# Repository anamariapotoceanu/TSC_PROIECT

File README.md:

# OpenBook E-Reader

OpenBook este un e-reader open-source construit in jurul microcontrollerului ESP32-C6-WROOM-1. Dispozitivul ofera o experienta de lectura cu afisaj e-paper, butoane fizice, conectivitate wireless si senzori de mediu integrati.

## DIAGRAMA BLOC

## BOM

| DENUMIRE | SITE ACHIZITIONARE | DATASHEET |
|----------|---------------------|-----------|
| BOOT_BUTON | [LINK](https://www.snapeda.com/parts/EVQP7L01P/Panasonic%20Electronic%20Components/view-part/?welcome=home) | [LINK](https://www.snapeda.com/parts/EVQP7L01P/Panasonic/datasheet/) |
| C1 - C10 | [LINK](https://componentsearchengine.com/part-view/CC0402MRX5R5BB106/YAGEO) | [LINK](https://componentsearchengine.com/Datasheets/2/CC0402MRX5R5BB106.pdf) |
| C1_BAT | [LINK](https://componentsearchengine.com/part-view/CC0402MRX5R5BB106/YAGEO) | [LINK](https://componentsearchengine.com/Datasheets/2/CC0402MRX5R5BB106.pdf) |
| C1_BAT2 | [LINK](https://componentsearchengine.com/part-view/CC0402MRX5R5BB106/YAGEO) | [LINK](https://componentsearchengine.com/Datasheets/2/CC0402MRX5R5BB106.pdf) |
| C2_BAT | [LINK](https://componentsearchengine.com/part-view/CC0402MRX5R5BB106/YAGEO) | [LINK](https://componentsearchengine.com/Datasheets/2/CC0402MRX5R5BB106.pdf) |
| C4_USB | [LINK](https://componentsearchengine.com/part-view/CC0402MRX5R5BB106/YAGEO) | [LINK](https://componentsearchengine.com/Datasheets/2/CC0402MRX5R5BB106.pdf) |
| C5_USB | [LINK](https://componentsearchengine.com/part-view/CC0402MRX5R5BB106/YAGEO) | [LINK](https://componentsearchengine.com/Datasheets/2/CC0402MRX5R5BB106.pdf) |
| C10_SUPERCAR | [LINK](https://industry.panasonic.com/global/en/products/control/switch/light-touch/number/evqpuj02k) | [LINK](https://industry.panasonic.com/global/en/downloads?tab=catalog&small_g_cd=203&part_no=EVQPUJ02K) |
| CHANGE_BUTTON | [LINK](https://www.snapeda.com/parts/EVQP7L01P/Panasonic%20Electronic%20Components/view-part/?welcome=home) | [LINK](https://www.snapeda.com/parts/EVQP7L01P/Panasonic/datasheet/) |
| CHG_LED | [LINK](https://www.snapeda.com/parts/KP-1608SURCK/Kingbright/view-part/?ref=search&t=LED%200603) | [LINK](https://www.snapeda.com/parts/KP-1608SURCK/Kingbright/datasheet/) |
| C_DELAY | [LINK](https://componentsearchengine.com/part-view/CC0402MRX5R5BB106/YAGEO) | [LINK](https://componentsearchengine.com/Datasheets/2/CC0402MRX5R5BB106.pdf) |
| D1 | [LINK](https://www.snapeda.com/parts/USBLC6-2SC6Y/STMicroelectronics/view-part/?ref=eda) | [LINK](https://www.snapeda.com/parts/USBLC6-2SC6Y/STMicroelectronics/view-part/?ref=eda) |
| D2 | [LINK](https://ro.mouser.com/ProductDetail/KYOCERA-AVX/SD0805S020S1R0?qs=jCA%252BPfw4LHbpkAoSnwrdjw%3D%3D) | [LINK](https://ro.mouser.com/datasheet/2/40/schottky-3165252.pdf) |
| D3 | [LINK](https://ro.mouser.com/ProductDetail/KYOCERA-AVX/SD0805S020S1R0?qs=jCA%252BPfw4LHbpkAoSnwrdjw%3D%3D) | [LINK](https://ro.mouser.com/datasheet/2/40/schottky-3165252.pdf) |
| D4 | [LINK](https://ro.mouser.com/ProductDetail/KYOCERA-AVX/SD0805S020S1R0?qs=jCA%252BPfw4LHbpkAoSnwrdjw%3D%3D) | [LINK](https://ro.mouser.com/datasheet/2/40/schottky-3165252.pdf) |
| D5 | [LINK](https://ro.mouser.com/ProductDetail/KYOCERA-AVX/SD0805S020S1R0?qs=jCA%252BPfw4LHbpkAoSnwrdjw%3D%3D) | [LINK](https://ro.mouser.com/datasheet/2/40/schottky-3165252.pdf) |
| D6 | [LINK](https://www.snapeda.com/parts/PGB1010603MR/Littelfuse/view-part/?ref=eda) | [LINK](https://www.snapeda.com/parts/PGB1010603MR/Littelfuse%20Inc./datasheet/) |
| D7 | [LINK](https://ro.mouser.com/ProductDetail/KYOCERA-AVX/SD0805S020S1R0?qs=jCA%252BPfw4LHbpkAoSnwrdjw%3D%3D) | [LINK](https://ro.mouser.com/datasheet/2/40/schottky-3165252.pdf) |
| D8 | [LINK](https://www.snapeda.com/parts/PGB1010603MR/Littelfuse/view-part/?ref=eda) | [LINK](https://www.snapeda.com/parts/PGB1010603MR/Littelfuse%20Inc./datasheet/) |
| D9 | [LINK](https://www.snapeda.com/parts/PGB1010603MR/Littelfuse/view-part/?ref=eda) | [LINK](https://www.snapeda.com/parts/PGB1010603MR/Littelfuse%20Inc./datasheet/) |
| D10 | [LINK](https://www.snapeda.com/parts/PGB1010603MR/Littelfuse/view-part/?ref=eda) | [LINK](https://www.snapeda.com/parts/PGB1010603MR/Littelfuse%20Inc./datasheet/) |
| D11 | [LINK](https://www.snapeda.com/parts/PGB1010603MR/Littelfuse/view-part/?ref=eda) | [LINK](https://www.snapeda.com/parts/PGB1010603MR/Littelfuse%20Inc./datasheet/) |
| D12 | [LINK](https://www.snapeda.com/parts/PGB1010603MR/Littelfuse/view-part/?ref=eda) | [LINK](https://www.snapeda.com/parts/PGB1010603MR/Littelfuse%20Inc./datasheet/) |
| EPD_C1 - EPD_C12 | [LINK](https://componentsearchengine.com/part-view/CC0402MRX5R5BB106/YAGEO) | [LINK](https://componentsearchengine.com/Datasheets/2/CC0402MRX5R5BB106.pdf) |
| IC1 | [LINK](https://componentsearchengine.com/part-view/BD5229G-TR/ROHM%20Semiconductor) | [LINK](https://datasheet.datasheetarchive.com/originals/distributors/Datasheets_SAMA/f2b9741ef86007909f138d561a359946.pdf) |
| IC4 | [LINK](https://componentsearchengine.com/part-view/XC6220A331MR-G/Torex) | [LINK](https://product.torexsemi.com/system/files/series/xc6220.pdf) |
| J1 | [LINK](https://componentsearchengine.com/part-view/FH34SRJ-24S-0.5SH(99)/Hirose) | [LINK](https://www.hirose.com/en/product/document?clcode=CL0580-1255-6-99&productname=FH34SRJ-24S-0.5SH(99)&series=FH34SRJ&documenttype=2DDrawing&lang=en&documentid=0000990903) |
| J2 | [LINK](https://componentsearchengine.com/part-view/USB4110-GF-A/GCT%20(GLOBAL%20CONNECTOR%20TECHNOLOGY)) | [LINK](https://gct.co/files/drawings/usb4110.pdf) |
| J3 | [LINK](https://www.snapeda.com/parts/PRT-14417/SparkFun/view-part/) | [LINK](https://www.snapeda.com/parts/PRT-14417/SparkFun%20Electronics/datasheet/) |
| J4 | [LINK](https://www.snapeda.com/parts/112A-TAAR-R03/Attend/view-part/) | [LINK](https://www.snapeda.com/parts/112A-TAAR-R03/Attend/datasheet/) |
| MCP73831 | [LINK](https://ro.mouser.com/ProductDetail/Microchip-Technology/MCP73831T-2ACI-OT?qs=yUQqVecv4qvbBQBGbHx0Mw%3D%3D&utm_id=20109199409&utm_source=google&utm_medium=cpc&utm_marketing_tactic=emeacorp&gad_source=1&gbraid=0AAAAADn_wf0-USzm1eg1ywGvQg_qMgG3H) | [LINK](https://ro.mouser.com/datasheet/2/268/MCP73831_Family_Data_Sheet_DS20001984H-3441711.pdf) |
| L1 | [LINK](https://ro.mouser.com/ProductDetail/Wurth-Elektronik/744043680?qs=PGXP4M47uW6VkZq%252BkzjrHA%3D%3D) | [LINK](https://www.we-online.com/components/products/datasheet/744043680.pdf) |
| PFMF.050.1 | [LINK](https://ro.mouser.com/ProductDetail/EPCOS-TDK/B72520T0350K062?qs=dEfas%2FXlABIszF52uu7vrg%3D%3D) | [LINK](https://www.tdk-electronics.tdk.com/inf/75/db/CTVS_14/Surge_protection_series.pdf) |
| Q1 | [LINK](https://componentsearchengine.com/part-view/DMG2305UX-7/Diodes%20Incorporated) | [LINK](https://www.diodes.com//assets/Datasheets/DMG2305UX.pdf) |
| Q2 | [LINK](https://componentsearchengine.com/part-view/DMG2305UX-7/Diodes%20Incorporated) | [LINK](https://www.diodes.com//assets/Datasheets/DMG2305UX.pdf) |
| Q3 | [LINK](https://componentsearchengine.com/part-view/SI1308EDL-T1-GE3/Vishay) | [LINK](https://componentsearchengine.com/part-view/SI1308EDL-T1-GE3/Vishay) |
| R1 - R10 | [LINK](https://componentsearchengine.com/part-view/R0402%201%25%20100%20K%20(RC0402FR-07100KL)/YAGEO) | [LINK](https://www.yageo.com/upload/media/product/products/datasheet/rchip/PYu-RC_Group_51_RoHS_L_12.pdf) |
| R1_PINH | [LINK](https://componentsearchengine.com/part-view/R0402%201%25%20100%20K%20(RC0402FR-07100KL)/YAGEO) | [LINK](https://www.yageo.com/upload/media/product/products/datasheet/rchip/PYu-RC_Group_51_RoHS_L_12.pdf) |
| R1_PINH1 | [LINK](https://componentsearchengine.com/part-view/R0402%201%25%20100%20K%20(RC0402FR-07100KL)/YAGEO) | [LINK](https://www.yageo.com/upload/media/product/products/datasheet/rchip/PYu-RC_Group_51_RoHS_L_12.pdf) |
| R1_BAT | [LINK](https://componentsearchengine.com/part-view/R0402%201%25%20100%20K%20(RC0402FR-07100KL)/YAGEO) | [LINK](https://www.yageo.com/upload/media/product/products/datasheet/rchip/PYu-RC_Group_51_RoHS_L_12.pdf) |
| R1_PWRUSB | [LINK](https://componentsearchengine.com/part-view/R0402%201%25%20100%20K%20(RC0402FR-07100KL)/YAGEO) | [LINK](https://www.yageo.com/upload/media/product/products/datasheet/rchip/PYu-RC_Group_51_RoHS_L_12.pdf) |
| R2_PINH | [LINK](https://componentsearchengine.com/part-view/R0402%201%25%20100%20K%20(RC0402FR-07100KL)/YAGEO) | [LINK](https://www.yageo.com/upload/media/product/products/datasheet/rchip/PYu-RC_Group_51_RoHS_L_12.pdf) |
| R2-PINH1 | [LINK](https://componentsearchengine.com/part-view/R0402%201%25%20100%20K%20(RC0402FR-07100KL)/YAGEO) | [LINK](https://www.yageo.com/upload/media/product/products/datasheet/rchip/PYu-RC_Group_51_RoHS_L_12.pdf) |
| R2_USB | [LINK](https://componentsearchengine.com/part-view/R0402%201%25%20100%20K%20(RC0402FR-07100KL)/YAGEO) | [LINK](https://www.yageo.com/upload/media/product/products/datasheet/rchip/PYu-RC_Group_51_RoHS_L_12.pdf) |
| R2_USB1 | [LINK](https://componentsearchengine.com/part-view/R0402%201%25%20100%20K%20(RC0402FR-07100KL)/YAGEO) | [LINK](https://www.yageo.com/upload/media/product/products/datasheet/rchip/PYu-RC_Group_51_RoHS_L_12.pdf) |
| RESET_BUTTON | [LINK](https://www.snapeda.com/parts/EVQP7L01P/Panasonic%20Electronic%20Components/view-part/?welcome=home) | [LINK](https://www.snapeda.com/parts/EVQP7L01P/Panasonic/datasheet/) |
| R_BOOT | [LINK](https://componentsearchengine.com/part-view/R0402%201%25%20100%20K%20(RC0402FR-07100KL)/YAGEO) | [LINK](https://www.yageo.com/upload/media/product/products/datasheet/rchip/PYu-RC_Group_51_RoHS_L_12.pdf) |
| R_CAPACITOR | [LINK](https://componentsearchengine.com/part-view/R0402%201%25%20100%20K%20(RC0402FR-07100KL)/YAGEO) | [LINK](https://www.yageo.com/upload/media/product/products/datasheet/rchip/PYu-RC_Group_51_RoHS_L_12.pdf) |
| R_CHANGE | [LINK](https://componentsearchengine.com/part-view/R0402%201%25%20100%20K%20(RC0402FR-07100KL)/YAGEO) | [LINK](https://www.yageo.com/upload/media/product/products/datasheet/rchip/PYu-RC_Group_51_RoHS_L_12.pdf) |
| R_CL1 | [LINK](https://componentsearchengine.com/part-view/R0402%201%25%20100%20K%20(RC0402FR-07100KL)/YAGEO) | [LINK](https://www.yageo.com/upload/media/product/products/datasheet/rchip/PYu-RC_Group_51_RoHS_L_12.pdf) |
| R_RESET | [LINK](https://componentsearchengine.com/part-view/R0402%201%25%20100%20K%20(RC0402FR-07100KL)/YAGEO) | [LINK](https://www.yageo.com/upload/media/product/products/datasheet/rchip/PYu-RC_Group_51_RoHS_L_12.pdf) |
| SENSOR2 | [LINK](https://www.snapeda.com/parts/BME680/Bosch/view-part/?welcome=home) | [LINK](https://www.snapeda.com/parts/BME680/Bosch%20Sensortec/datasheet/) |
| TP | [nan](nan) | [nan](nan) |
| U1 | [LINK](https://www.snapeda.com/parts/W25Q512JVEIQ/Winbond+Electronics/view-part/?ref=eda) | [LINK](https://www.snapeda.com/parts/W25Q512JVEIQ/Winbond+Electronics/view-part/?ref=eda) |
| U2 | [LINK](https://www.snapeda.com/parts/ESP32-C6-WROOM-1-N8/Espressif+Systems/view-part/?ref=eda) | [LINK](https://www.snapeda.com/parts/ESP32-C6-WROOM-1-N8/Espressif%20Systems/datasheet/) |
| U3 | [LINK](https://www.snapeda.com/parts/DS3231SN%23/Analog+Devices/view-part/?ref=eda) | [LINK](https://www.snapeda.com/parts/DS3231SN%23/Analog%20Devices/datasheet/) |
| U4 | [LINK](https://www.snapeda.com/parts/MAX17048G+T10/Analog+Devices/view-part/?ref=eda) | [LINK ](https://www.snapeda.com/parts/MAX17048G+T10/Analog%20Devices/datasheet/) |

## Functionalitate hardware detaliata

OpenBook este un e-reader open-source construit in jurul microcontrollerului ESP32-C6-WROOM-1-N8. Sistemul este modular si a fost gandit pentru consum redus de energie, simplitate si extensibilitate.

### Microcontroller - ESP32-C6-WROOM-1-N8
- Procesor RISC-V 32-bit, frecventa 160 MHz+
- Suport pentru Wi-Fi 6, BLE 5 si USB 2.0 FS
- Interfete disponibile: SPI, I2C, UART, GPIO
- Consum redus: aproximativ 60 mA in activ, sub 100 uA in deep sleep

### Display - E-Paper 7.5 inch (Waveshare)
- Rezolutie 800x480 alb-negru
- Interfata SPI, partajata cu alte periferice
- Foloseste linii dedicate pentru ceas, date, comenzi, reset si status
- Consum doar in timpul refreshului (~30 - 50 mA)

### Senzori de mediu
- **BME688** masoara temperatura, umiditatea, presiunea si calitatea aerului
- Conectat pe magistrala I2C, alaturi de RTC si fuel gauge
- **DS3231**  este un RTC cu backup pe supercapacitor si semnal de intrerupere catre microcontroller
- **MAX17048** (fuel gauge): I2C + ALERT pe IO16
- Un fuel gauge care poate trimite alerta in caz de nivel scazut

### Memorie externa
- W25Q512J, o memorie NOR Flash de 64MB, conectata prin SPI
- Are chip select dedicat pentru acces independent de afisaj

### SD Card (optional)
- Suportat pe aceeasi magistrala SPI cu chip select separat
- Permite extinderea capacitatii de stocare

### Butoane
- Trei butoane tactile conectate direct la pinii microcontrollerului
- Sunt folosite pentru navigare si selectie in interfata
- Gestionate prin intreruperi, cu debounce hardware si software

### Alimentare
- Sistemul este alimentat de o baterie Li-Po de 2500 mAh
- Incarcarea se face prin USB-C cu ajutorul unui MCP73831
- Un semnal digital permite monitorizarea starii de incarcare
- Tensiunea este stabilizata la 3.3V printr-un LDO

### USB-C
- Asigura incarcare si transfer de fisiere in mod MSC (Mass Storage)
- Liniile USB sunt protejate cu diode ESD

### Consum estimativ
- In activ cu Wi-Fi: intre 60 si 100 mA
- In activ fara Wi-Fi: intre 40 si 60 mA
- In standby: aproximativ 10 mA
- In deep sleep: sub 100 uA

### PCB si carcasa
- Placa in 2 straturi, rutare clara pentru alimentare si SPI
- Separare intre zonele digitale si analogice
- Carcasa ABS/PC, usoara si ergonomica

| IO Pin | Semnal     | Rol                                               |
|--------|------------|----------------------------------------------------|
| EN | RESET  | Semnal de intrare pentru resetare |
| 0| INT_RTC | Semnal de intrerupere generat de modulul RTC |
| 1 | 32KHZ | Oscilator 32kHz pentru RTC |
| 2 | MISO | SPI MISO date de la periferice |
| 3 | EPD_BUSY | Semnal ocupat de la afisaj e-paper |
| 4 | SS_SD | Chip Select pentru SD Card |
| 5 | EPD_DC | Comanda date/controle pentru e-paper |
| 6 | SCK | SPI Clock comun pentru SD, flash si e-paper |
| 7 | MOSI | SPI MOSI date catre SD, flash, e-paper |
| 8 | GPIO8 | Selectarea cardului SD |
| 9 | IO/BOOT | Mod de boot selectabil |
| 10 | EPD_CS | Chip Select pentru afisaj e-paper |
| 11 | FLASH_CS | Chip Select pentru flash NOR |
| 12 | USB_D- | Linie pozitiva pentru USB Full-Speed |
| 13 | USB_D+ | Linie pozitiva pentru USB Full-Speed |
| 14 | NEUTILIZAT | NEUTILIZAT |
| 15 | IO/CHANGE | Detectarea modificarii starii |
| 16 | TX | Debug |
| 17 | RX | Debug |
| 18 | RTC_RST | Reset pentru modulul RTC|
| 19 | I2C_PW | Gestionarea alimentarii pentru dispozitivele I2C |
| 20 | EPD_3V3_C | Gestionarea alimentarii display-ului |
| 21 | SDA | I2C SDA conexiune alternativa RTC |
| 22 | SCL | I2C SCL conexiune alternativa RTC |
| 23 | EPD_RST | Reset alternativ e-paper display |

## Erori

Am aprobat erorile din schematic deoarece alimentarile sunt corecte din punct de vedere hardware.

Am aprobat erorile de DRC aparute la mufa USB din cauza celor doua gauri, deoarece acestea sunt conforme cu specificatiile
mecanice ale mufei si nu afecteaza functionalitatea.

## Imagini

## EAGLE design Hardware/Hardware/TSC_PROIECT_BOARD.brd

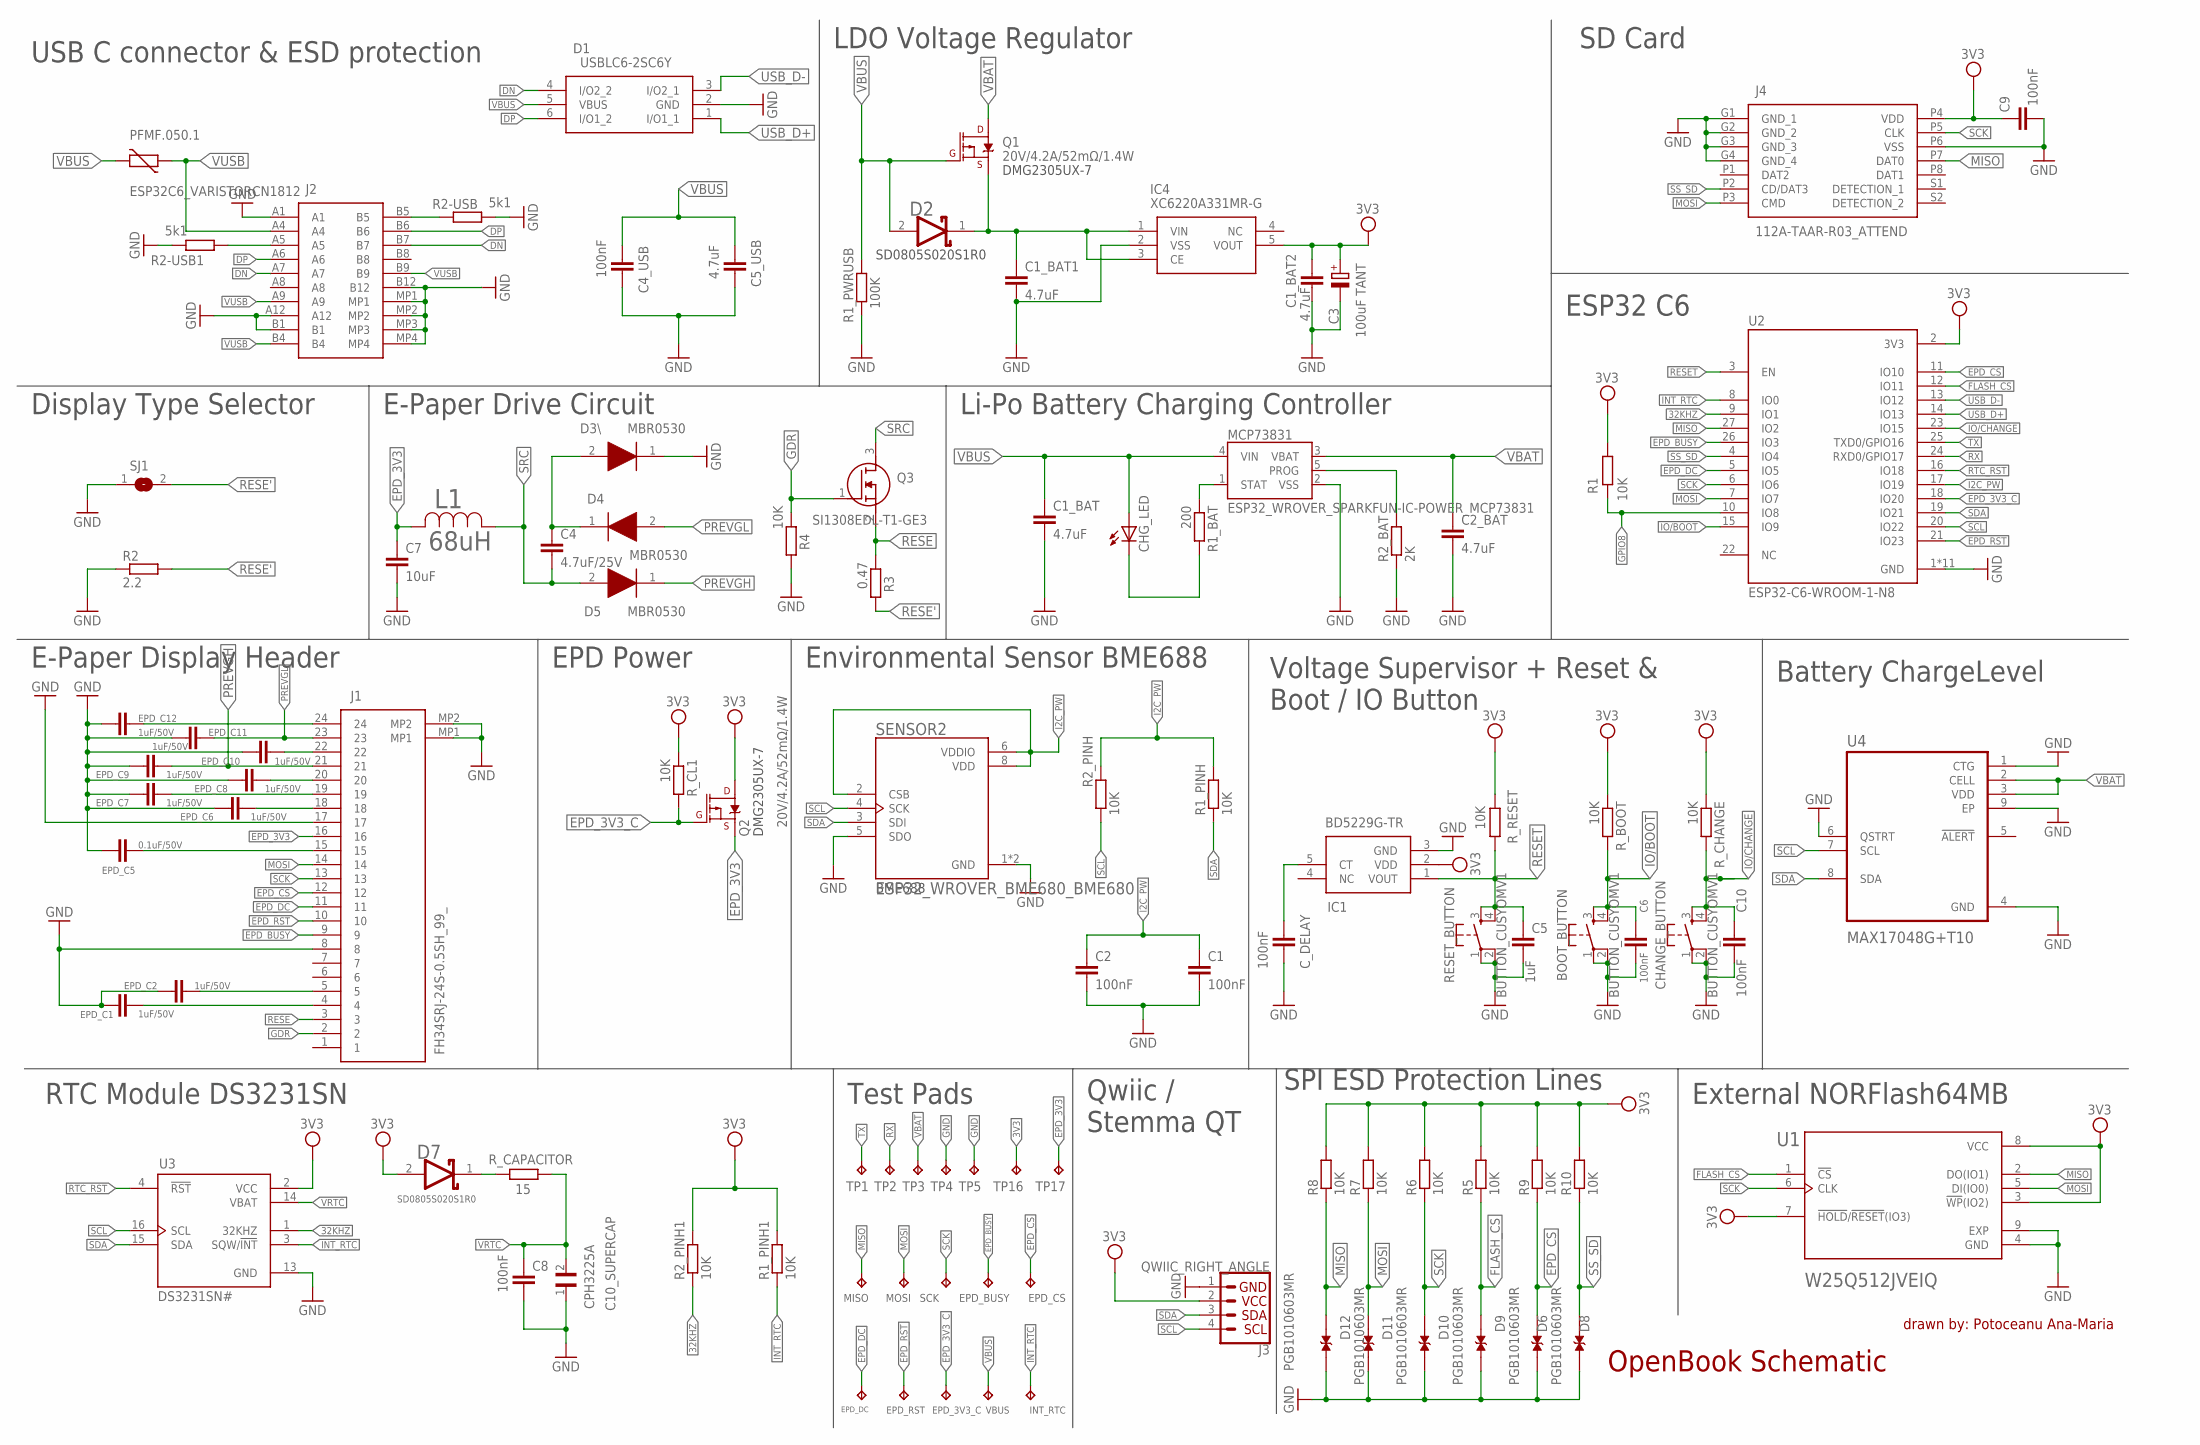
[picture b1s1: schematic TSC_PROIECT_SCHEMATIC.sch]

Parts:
BOOT_BUTTON: BUTTON_CUSYOMV1; MYBUTTON
C1, C2, C4_USB, C6, C8, C9, C10: 100nF; ESP32_WROVER_EAGLE-LTSPICE_C0402
C1_BAT, C1_BAT1, C1_BAT2, C2_BAT, C5_USB: 4.7uF; ESP32_WROVER_EAGLE-LTSPICE_C0402
C3: 100uF TANT; RCL_CT3528
C4: 4.7uF/25V; ESP32_WROVER_EAGLE-LTSPICE_C0402
C5: 1uF; ESP32_WROVER_EAGLE-LTSPICE_C0402
C7: 10uF; ESP32_WROVER_EAGLE-LTSPICE_C0402
C10_SUPERCAP: CPH3225A; CAPCP3225X100N
CHANGE_BUTTON: BUTTON_CUSYOMV1; MYBUTTON
CHG_LED: ADAFRUIT_LEDCHIP-LED0603; ADAFRUIT_CHIP-LED0603
C_DELAY: 100nF; ESP32_WROVER_EAGLE-LTSPICE_C0402
D1: USBLC6-2SC6Y; SOT95P280X145-6N
D2, D7: ESP32_WROVER_AVX---SD0805S020S1R0_AVX_SD0805S020S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; ESP32_WROVER_AVX---SD0805S020S1R0_AVX_SD0805S020S1R0_0
D3\, D4, D5: MBR0530; SOD3716X135N
D6, D8, D9, D10, D11, D12: PGB1010603MR; DIOC1608X36N
EPD_3V3_C: TPTP20R; TP20R
EPD_BUSY: TPTP20R; TP20R
EPD_C1, EPD_C2, EPD_C6, EPD_C7, EPD_C8, EPD_C9, EPD_C10, EPD_C11, EPD_C12: 1uF/50V; ESP32_WROVER_EAGLE-LTSPICE_C0402
EPD_C5: 0.1uF/50V; ESP32_WROVER_EAGLE-LTSPICE_C0402
EPD_CS: TPTP20R; TP20R
EPD_DC: TPTP20R; TP20R
EPD_RST: TPTP20R; TP20R
IC1: BD5229G-TR; SOT95P280X125-5N
IC4: XC6220A331MR-G; SOT95P280X120-5N
INT_RTC: TPTP20R; TP20R
J1: FH34SRJ-24S-0.5SH_99_; FH34SRJ24S05SH99
J2: SAMACSYS_PARTS_USB4110-GF-A; SAMACSYS_PARTS_USB4110GFA
J3: QWIIC_RIGHT_ANGLE; JST04_1MM_RA
J4: 112A-TAAR-R03_ATTEND; 112ATAARR03ATTEND
L1: 68uH; IND_4828-WE-TPC_WRE
MCP73831: ESP32_WROVER_SPARKFUN-IC-POWER_MCP73831; ESP32_WROVER_SPARKFUN-IC-POWER_SOT23-5
MISO: TPTP20R; TP20R
MOSI: TPTP20R; TP20R
PFMF.050.1: ESP32C6_VARISTORCN1812; ESP32C6_VARISTOR_CT/CN1812
Q1, Q2: 20V/4.2A/52mΩ/1.4W; ESP32_WROVER_SPARKFUN-DISCRETESEMI_SOT23-3
Q3: SI1308EDL-T1-GE3; SOT65P210X110-3N
R1, R1_PINH, R1_PINH1, R2_PINH, R2_PINH1, R4, R5, R6, R7, R8, R9, R10: 10K; ESP32_WROVER_EAGLE-LTSPICE_R0402
R1_BAT: 200; ESP32_WROVER_EAGLE-LTSPICE_R0402
R1_PWRUSB: 100K; ESP32_WROVER_EAGLE-LTSPICE_R0402
R2: 2.2; ESP32_WROVER_EAGLE-LTSPICE_R0402
R2-USB, R2-USB1: 5k1; ESP32_WROVER_EAGLE-LTSPICE_R0402
R2_BAT: 2K; ESP32_WROVER_EAGLE-LTSPICE_R0402
R3: 0.47; ESP32_WROVER_EAGLE-LTSPICE_R0402
RESET_BUTTON: BUTTON_CUSYOMV1; MYBUTTON
R_BOOT: 10K; ESP32_WROVER_EAGLE-LTSPICE_R0402
R_CAPACITOR: 15; ESP32_WROVER_EAGLE-LTSPICE_R0402
R_CHANGE: 10K; ESP32_WROVER_EAGLE-LTSPICE_R0402
R_CL1: 10K; ESP32_WROVER_EAGLE-LTSPICE_R0402
R_RESET: 10K; ESP32_WROVER_EAGLE-LTSPICE_R0402
SCK: TPTP20R; TP20R
SENSOR2: ESP32_WROVER_BME680_BME680; ESP32_WROVER_BME680_PSON80P300X300X100-8N
SJ1: SJ
TP1, TP2, TP3, TP4, TP5, TP16, TP17: TPTP20R; TP20R
U1: W25Q512JVEIQ; SON127P600X800X80-9N
U2: ESP32-C6-WROOM-1-N8; XCVR_ESP32-C6-WROOM-1-N8
U3: DS3231SN#; SOIC127P1032X265-16N
U4: MAX17048G+T10; SON50P200X200X80-9N
VBUS: TPTP20R; TP20R

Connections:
3V3: C1_BAT2.1, C3.+, C9.1, D7.2 (ANODE), IC1.2 (VDD), IC4.5 (VOUT), J3.2, J4.P4 (VDD), Q2.3 (D), R1.1, R1_PINH1.2, R2_PINH1.2, R5.2, R6.2, R7.2, R8.2, R9.2, R10.2, R_BOOT.1, R_CHANGE.1, R_CL1.1, R_RESET.1, TP16.TP, U1.3 (!WP!(IO2)), U1.7 (!HOLD!/!RESET!(IO3)), U1.8 (VCC), U2.2 (3V3), U3.2 (VCC)
32KHZ: R2_PINH1.1, U2.9 (IO1), U3.1 (32KHZ)
DN: D1.4 (I/O2_2), J2.A7, J2.B7
DP: D1.6 (I/O1_2), J2.A6, J2.B6
EPD_3V3: C7.1, J1.16, L1.2, Q2.2 (S), TP17.TP
EPD_3V3_C: EPD_3V3_C.TP, Q2.1 (G), R_CL1.2, U2.18 (IO20)
EPD_BUSY: EPD_BUSY.TP, J1.9, U2.26 (IO3)
EPD_CS: D6.1, EPD_CS.TP, J1.12, R9.1, U2.11 (IO10)
EPD_DC: EPD_DC.TP, J1.11, U2.5 (IO5)
EPD_RST: EPD_RST.TP, J1.10, U2.21 (IO23)
FLASH_CS: D9.1, R5.1, U1.1 (!CS), U2.12 (IO11)
GDR: J1.2, Q3.1 (G), R4.1
GND: BOOT_BUTTON.1, BOOT_BUTTON.2, C1.2, C1_BAT.2, C1_BAT1.2, C1_BAT2.2, C2.2, C2_BAT.2, C3.-, C4_USB.2, C5.2, C5_USB.2, C6.2, C7.2, C8.2, C9.2, C10.2, C10_SUPERCAP.1, CHANGE_BUTTON.1, CHANGE_BUTTON.2, C_DELAY.2, D1.2 (GND), D3\.1 (K), D6.2, D8.2, D9.2, D10.2, D11.2, D12.2, EPD_C1.2, EPD_C2.2, EPD_C5.2, EPD_C6.2, EPD_C7.2, EPD_C8.2, EPD_C9.2, EPD_C10.2, EPD_C11.2, EPD_C12.2, IC1.3 (GND), IC4.2 (VSS), J1.8, J1.17, J1.MP1, J1.MP2, J2.A1, J2.A12, J2.B1, J2.B12, J2.MP1, J2.MP2, J2.MP3, J2.MP4, J3.1, J4.G1 (GND_1), J4.G2 (GND_2), J4.G3 (GND_3), J4.G4 (GND_4), J4.P6 (VSS), MCP73831.2 (VSS), R1_PWRUSB.1, R2.1, R2-USB.2, R2-USB1.1, R2_BAT.1, R4.2, RESET_BUTTON.1, RESET_BUTTON.2, SENSOR2.1 (GND), SENSOR2.5 (SDO), SENSOR2.7 (GND), SJ1.1, TP4.TP, TP5.TP, U1.4 (GND), U1.9 (EXP), U2.1 (GND), U2.28 (GND), U2.29_1 (GND), U2.29_2 (GND), U2.29_3 (GND), U2.29_4 (GND), U2.29_5 (GND), U2.29_6 (GND), U2.29_7 (GND), U2.29_8 (GND), U2.29_9 (GND), U3.13 (GND), U4.1 (CTG), U4.4 (GND), U4.6 (QSTRT), U4.9 (EP)
GPIO8: R1.2, U2.10 (IO8)
I2C_PW: C1.1, C2.1, R1_PINH.2, R2_PINH.2, SENSOR2.2 (CSB), SENSOR2.6 (VDDIO), SENSOR2.8 (VDD), U2.17 (IO19)
INT_RTC: INT_RTC.TP, R1_PINH1.1, U2.8 (IO0), U3.3 (SQW/!INT)
IO/BOOT: BOOT_BUTTON.3, BOOT_BUTTON.4, C6.1, R_BOOT.2, U2.15 (IO9)
IO/CHANGE: C10.1, CHANGE_BUTTON.3, CHANGE_BUTTON.4, R_CHANGE.2, U2.23 (IO15)
MISO: D12.1, J4.P7 (DAT0), MISO.TP, R8.1, U1.2 (DO(IO1)), U2.27 (IO2)
MOSI: D11.1, J1.14, J4.P3 (CMD), MOSI.TP, R7.1, U1.5 (DI(IO0)), U2.7 (IO7)
unnamed: J2.B5, R2-USB.1
unnamed: J2.A5, R2-USB1.2
unnamed: C1_BAT1.1, D2.1 (CATHODE), IC4.1 (VIN), IC4.3 (CE), Q1.2 (S)
unnamed: C4.1, D3\.2 (A), D4.1 (K)
unnamed: EPD_C10.1, J1.22
unnamed: EPD_C5.1, J1.15
unnamed: CHG_LED.C, R1_BAT.2
unnamed: MCP73831.1 (STAT), R1_BAT.1
unnamed: EPD_C8.1, J1.20
unnamed: MCP73831.5 (PROG), R2_BAT.2
unnamed: EPD_C2.1, J1.5
unnamed: D7.1 (CATHODE), R_CAPACITOR.2
unnamed: C_DELAY.1, IC1.5 (CT)
unnamed: EPD_C12.1, J1.24
unnamed: EPD_C7.1, J1.19
unnamed: EPD_C1.1, J1.4
unnamed: EPD_C6.1, J1.18
PREVGH: D5.1 (K), EPD_C9.1, J1.21
PREVGL: D4.2 (A), EPD_C11.1, J1.23
RESE: J1.3, Q3.2 (S), R3.1
RESE': R2.2, R3.2, SJ1.2
RESET: C5.1, IC1.1 (VOUT), RESET_BUTTON.3, RESET_BUTTON.4, R_RESET.2, U2.3 (EN)
RTC_RST: U2.16 (IO18), U3.4 (!RST)
RX: TP2.TP, U2.24 (RXD0/GPIO17)
SCK: D10.1, J1.13, J4.P5 (CLK), R6.1, SCK.TP, U1.6 (CLK), U2.6 (IO6)
SCL: J3.4, R2_PINH.1, SENSOR2.4 (SCK), U2.20 (IO22), U3.16 (SCL), U4.7 (SCL)
SDA: J3.3, R1_PINH.1, SENSOR2.3 (SDI), U2.19 (IO21), U3.15 (SDA), U4.8 (SDA)
SRC: C4.2, D5.2 (A), L1.1, Q3.3 (D)
SS_SD: D8.1, J4.P2 (CD/DAT3), R10.1, U2.4 (IO4)
TX: TP1.TP, U2.25 (TXD0/GPIO16)
USB_D+: D1.1 (I/O1_1), U2.14 (IO13)
USB_D-: D1.3 (I/O2_1), U2.13 (IO12)
VBAT: C2_BAT.1, MCP73831.3 (VBAT), Q1.3 (D), TP3.TP, U4.2 (CELL), U4.3 (VDD)
VBUS: C1_BAT.1, C4_USB.1, C5_USB.1, CHG_LED.A, D1.5 (VBUS), D2.2 (ANODE), MCP73831.4 (VIN), PFMF.050.1.2, Q1.1 (G), R1_PWRUSB.2, VBUS.TP
VRTC: C8.1, C10_SUPERCAP.2, R_CAPACITOR.1, U3.14 (VBAT)
VUSB: J2.A4, J2.A9, J2.B4, J2.B9, PFMF.050.1.1

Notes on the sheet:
SD0805S020S1R0
DMG2305UX-7
BME688
USB C connector & ESD protection
LDO Voltage Regulator
SD Card
Display Type Selector
E-Paper Drive Circuit
Li-Po Battery Charging Controller
ESP32 C6
E-Paper Display Header
EPD Power
Environmental Sensor BME688
Voltage Supervisor + Reset & Boot / IO Button
Battery ChargeLevel
RTC Module DS3231SN
Test Pads
Qwiic / Stemma QT
SPI ESD Protection Lines
External NORFlash64MB
drawn by: Potoceanu Ana-Maria
OpenBook Schematic

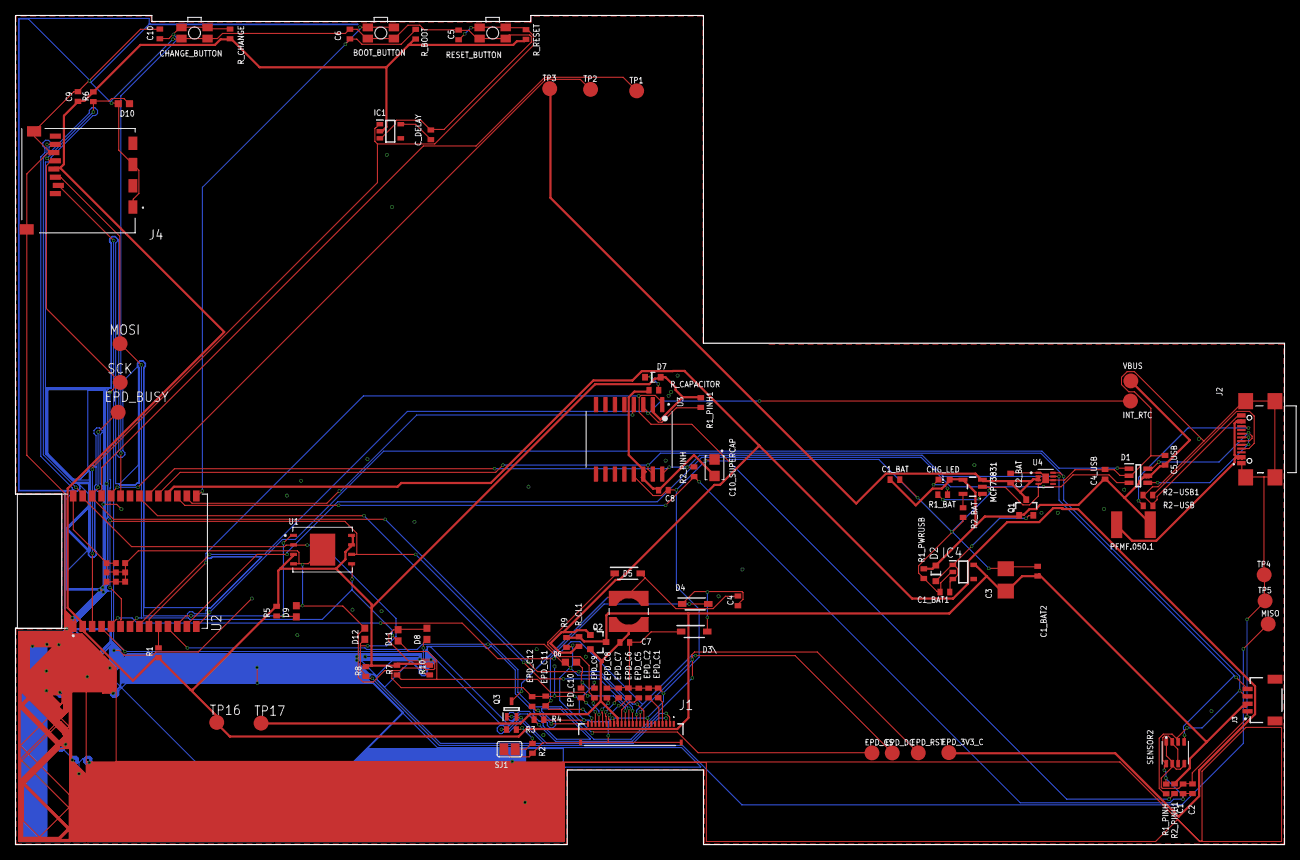
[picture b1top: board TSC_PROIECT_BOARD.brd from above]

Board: 2 copper layers, 170.2 x 111.2 mm, 103 parts (0 on the bottom side), 56 nets.

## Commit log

2025-04-06 Add files via upload
    Am adaugat in folderul Hardware, schematicul si boardul din Fusion, carora le-am dat Export.
2025-04-06 Add files via upload
    Am adaugat folderul Manufacturing care contine gerbers.zip, Bill_of_Materials si Pick_and_Place.csv
2025-04-06 Add files via upload
    Am adaugat fisierul 3D cu dispozitivul complet (PCB + baterie + display + carcasa) si fisierul 3D Fusion360 cu dispozitivul complet.
2025-04-06 Add files via upload
    Am adaugat fisierul 3D cu dispozitivul complet (PCB + baterie + display + carcasa) (.step) si fisierul 3D Fusion360 cu dispozitivul complet(.f3z)
2025-04-06 Add files via upload
    Am adaugat imagini relevante din proiect.
2025-04-06 Add files via upload
    Am adaugat diagrama bloc.
2025-04-06 Create LICENSE
2025-04-06 Add files via upload
    Am adaugat animatia in format .mp4.

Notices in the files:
parts and their libraries:
COPYRIGHT: Copyright (C) 2024 Ultra Librarian. All rights reserved.
